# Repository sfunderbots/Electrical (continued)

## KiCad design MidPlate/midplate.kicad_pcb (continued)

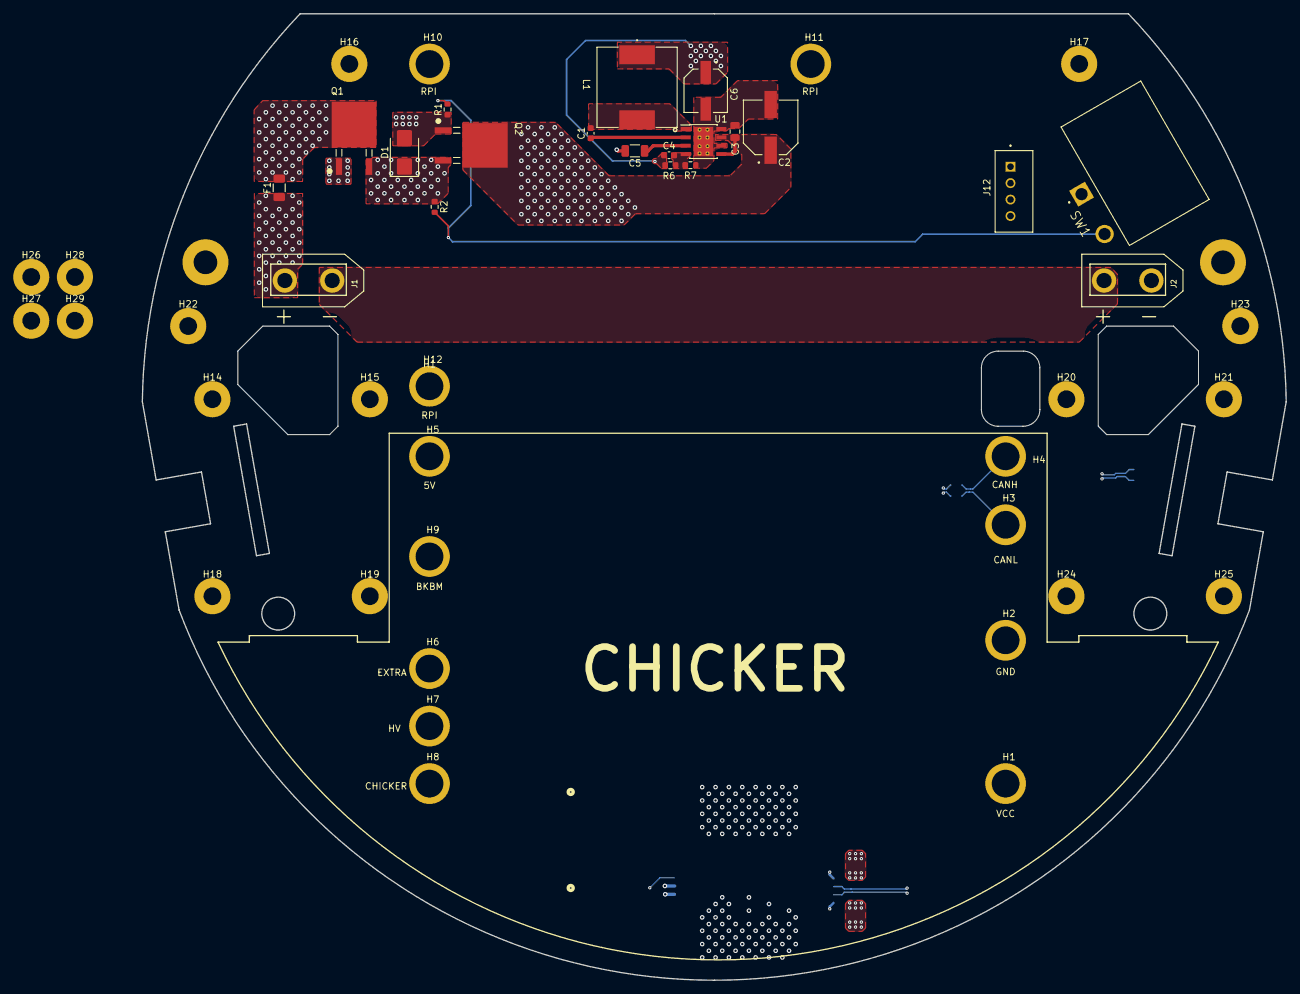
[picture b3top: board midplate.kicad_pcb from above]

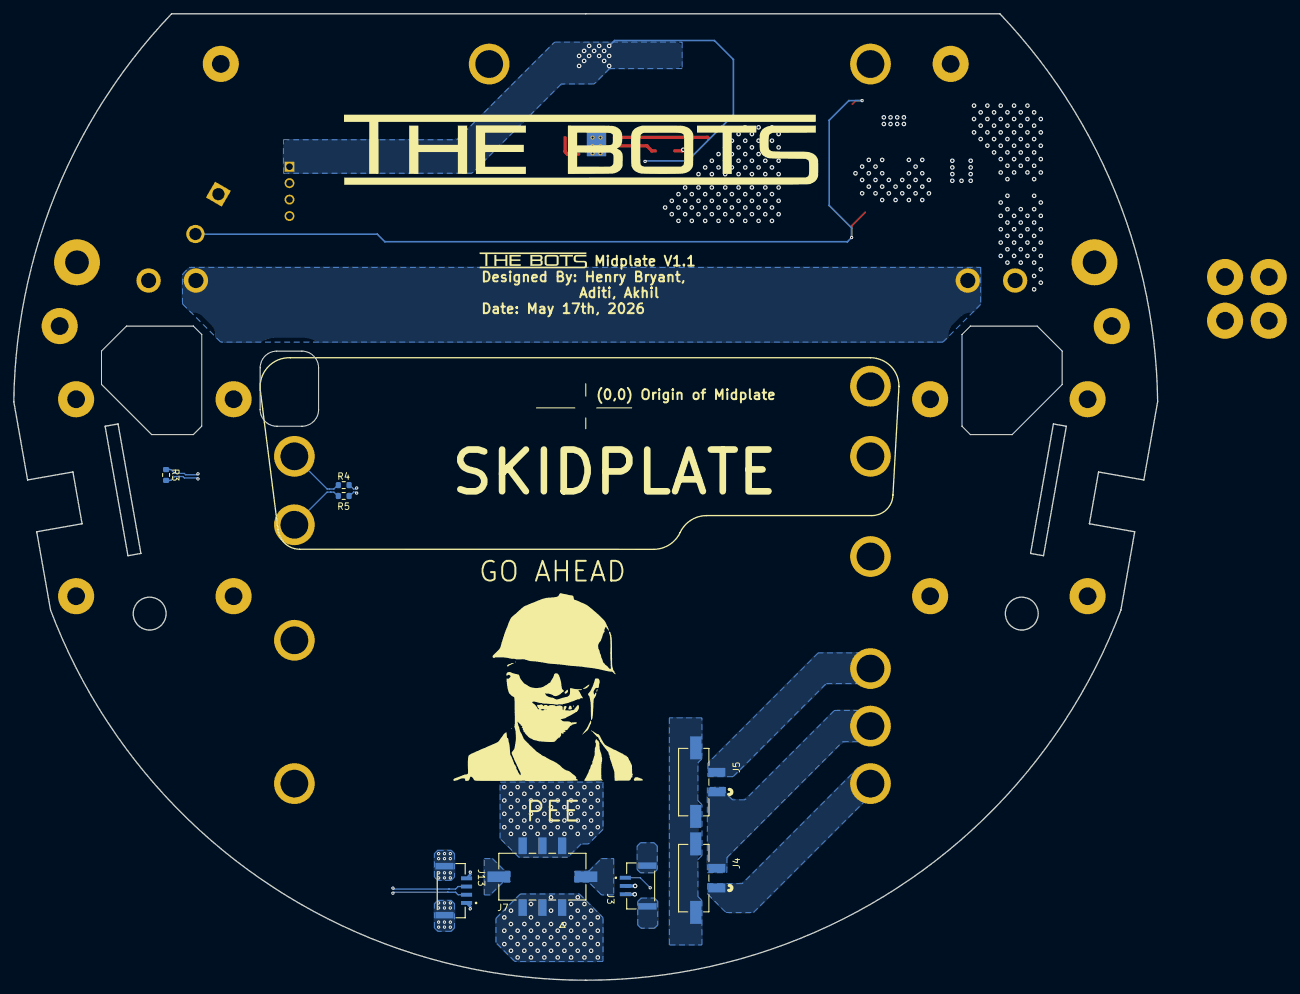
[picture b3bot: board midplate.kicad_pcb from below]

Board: 4 copper layers, 174.0 x 147.0 mm, 59 parts (8 on the bottom side), 22 nets.

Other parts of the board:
H1#2: RPI; MountingHole_2.7mm_M2.5_DIN965_Pad
H47, H48: MountingHoleM2.5NoThread; MountingHole_3.6mm_M3_clearance

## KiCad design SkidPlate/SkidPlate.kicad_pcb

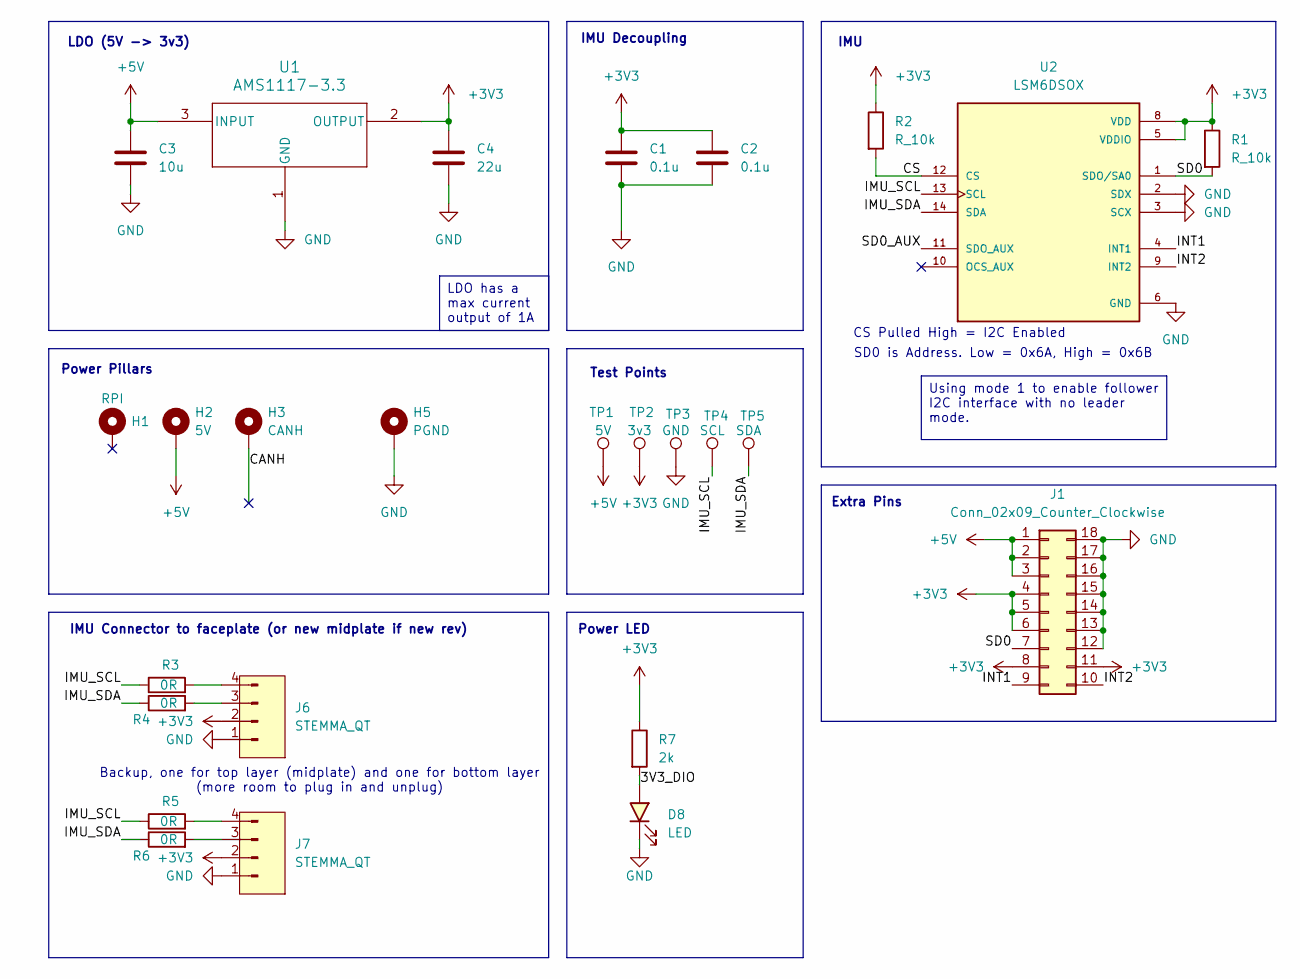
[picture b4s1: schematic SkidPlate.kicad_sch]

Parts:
C1, C2: 0.1u; C_0603_1608Metric; MPN CC0603KRX7R9BB104; JLC 0603
C3: 10u; C_0805_2012Metric; MPN GRM21BR61H106KE43L; JLC 0805
C4: 22u; C_0603_1608Metric; LCSC C59461
D8: LED; LED_0805_2012Metric; MPN KT-0805G; JLC 0805
H1: RPI; MountingHole_2.7mm_M2.5_DIN965_Pad
H2: 5V; MountingHole_2.7mm_M2.5_DIN965_Pad
H3: CANH; MountingHole_2.7mm_M2.5_DIN965_Pad
H5: PGND; MountingHole_2.7mm_M2.5_DIN965_Pad
J1: Conn_02x09_Counter_Clockwise; PinHeader_2x09_P2.54mm_Vertical
J6, J7: STEMMA_QT; JST_SH_BM04B-SRSS-TB_1x04-1MP_P1.00mm_Vertical
R1, R2: R_10k; R_0603_1608Metric; MPN 0603WAF1002T5E; JLC 0603
R3, R4, R5, R6: 0R; R_0603_1608Metric; MPN 0603WAF0000T5E; JLC 0603
R7: 2k; R_0603_1608Metric; MPN 0603WAF2001T5E; JLC 0603
TP1: 5V; TestPoint_Pad_D1.0mm
TP2: 3v3; TestPoint_Pad_D1.0mm
TP3: GND; TestPoint_Pad_D1.0mm
TP4: SCL; TestPoint_Pad_D1.0mm
TP5: SDA; TestPoint_Pad_D1.0mm
U1: AMS1117-3.3; SOT-223-3_TabPin2; MPN AMS1117-3.3; JLC SOT-223
U2: LSM6DSOX; PQFN50P250X300X86-14N; PARTREV 3.0; JLC LGA-14(2.5x3)

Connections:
+3V3: C1.1, C2.1, C4.1, J1.4, J1.5, J1.6, J1.8, J1.11, J6.2, J7.2, R1.1, R2.1, R7.1, TP2.1 (1_1), U1.2 (OUTPUT), U2.5 (VDDIO), U2.8 (VDD)
+5V: C3.1, H2.1 (1_1), J1.1, J1.2, J1.3, TP1.1 (1_1), U1.3 (INPUT)
/3V3_DIO: D8.2 (A), R7.2
/CANH: H3.1 (1_1)
/CS: R2.2, U2.12 (CS)
/IMU_SCL: R3.1, R5.1, TP4.1 (1_1), U2.13 (SCL)
/IMU_SDA: R4.1, R6.1, TP5.1 (1_1), U2.14 (SDA)
/INT1: J1.9, U2.4 (INT1)
/INT2: J1.10, U2.9 (INT2)
/SD0: J1.7, R1.2, U2.1 (SDO/SA0)
/SD0_AUX: U2.11 (SDO_AUX)
GND: C1.2, C2.2, C3.2, C4.2, D8.1 (K), H5.1 (1_1), J1.12, J1.13, J1.14, J1.15, J1.16, J1.17, J1.18, J6.1, J7.1, TP3.1 (1_1), U1.1 (GND), U2.2 (SDX), U2.3 (SCX), U2.6 (GND), U2.7 (GND)
unnamed: J6.3, R4.2
unnamed: J6.4, R3.2
unnamed: J7.3, R6.2
unnamed: J7.4, R5.2

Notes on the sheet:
IMU Connector to faceplate (or new midplate if new rev)
Backup, one for top layer (midplate) and one for bottom layer (more room to plug in and unplug)
Extra Pins
Test Points
IMU
CS Pulled High = I2C Enabled
Power Pillars
Power LED
LDO (5V -> 3v3)
IMU Decoupling
SD0 is Address. Low = 0x6A, High = 0x6B
LDO has a max current output of 1A
Using mode 1 to enable follower I2C interface with no leader mode.

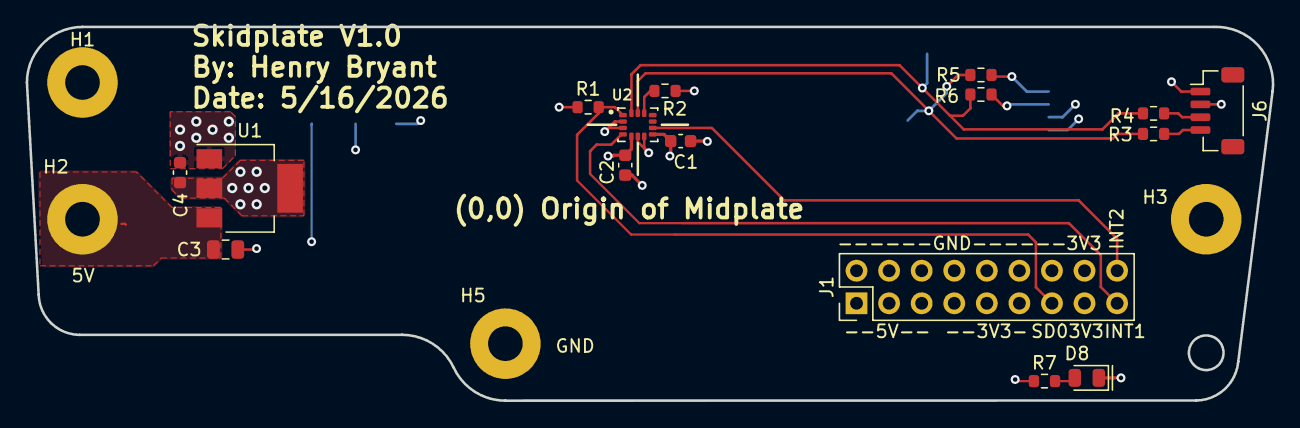
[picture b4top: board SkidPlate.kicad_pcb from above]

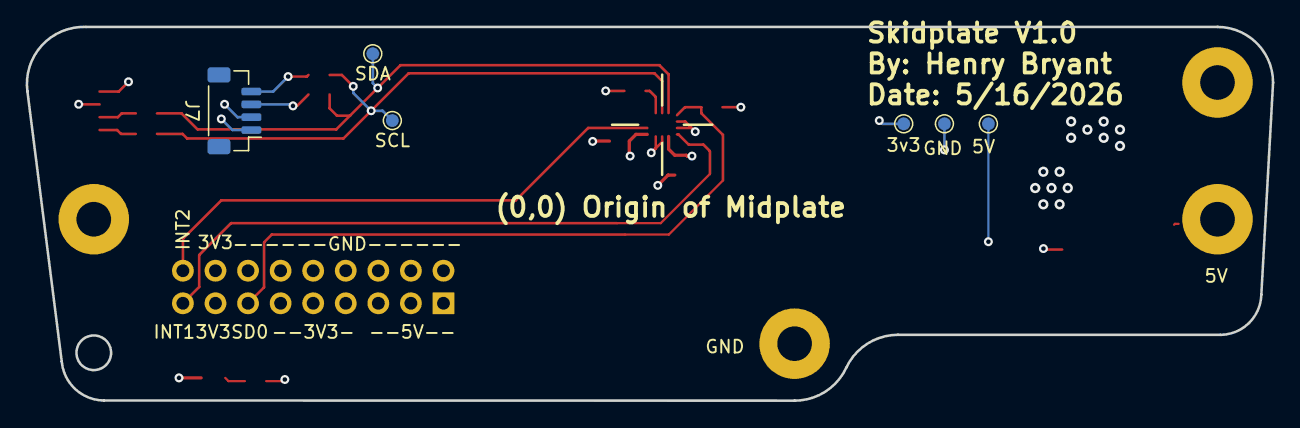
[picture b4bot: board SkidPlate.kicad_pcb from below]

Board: 4 copper layers, 97.2 x 29.1 mm, 26 parts (6 on the bottom side), 14 nets.

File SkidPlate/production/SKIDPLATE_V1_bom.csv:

Designator,Footprint,Quantity,Value,LCSC Part #
"C1, C2",0603,2,0.1u,C14663
C3,0805,1,10u,C440198
C4,0603,1,22u,C59461
D8,0805,1,LED,C2297
H2,MountingHole_2.7mm_M2.5_DIN965_Pad,1,PGND,
H5,MountingHole_2.7mm_M2.5_DIN965_Pad,1,5V,
H6,MountingHole_2.7mm_M2.5_DIN965_Pad,1,EXTRA,
H9,MountingHole_2.7mm_M2.5_DIN965_Pad,1,BKBM,
J1,PinHeader_2x09_P2.54mm_Vertical,1,Conn_02x09_Counter_Clockwise,
"J6, J7",JST_SH_BM04B-SRSS-TB_1x04-1MP_P1.00mm_Vertical,2,STEMMA_QT,
"R1, R2",0603,2,R_10k,C25804
"R3, R4, R5, R6",0603,4,0R,C21189
R7,0603,1,2k,C22975
TP1,TestPoint_Pad_D1.0mm,1,5V,
TP2,TestPoint_Pad_D1.0mm,1,3v3,
TP3,TestPoint_Pad_D1.0mm,1,GND,
TP4,TestPoint_Pad_D1.0mm,1,SCL,
TP5,TestPoint_Pad_D1.0mm,1,SDA,
U1,SOT-223-3_TabPin2,1,AMS1117-3.3,C6186
U2,PQFN50P250X300X86-14N,1,LSM6DSOX,C2655100

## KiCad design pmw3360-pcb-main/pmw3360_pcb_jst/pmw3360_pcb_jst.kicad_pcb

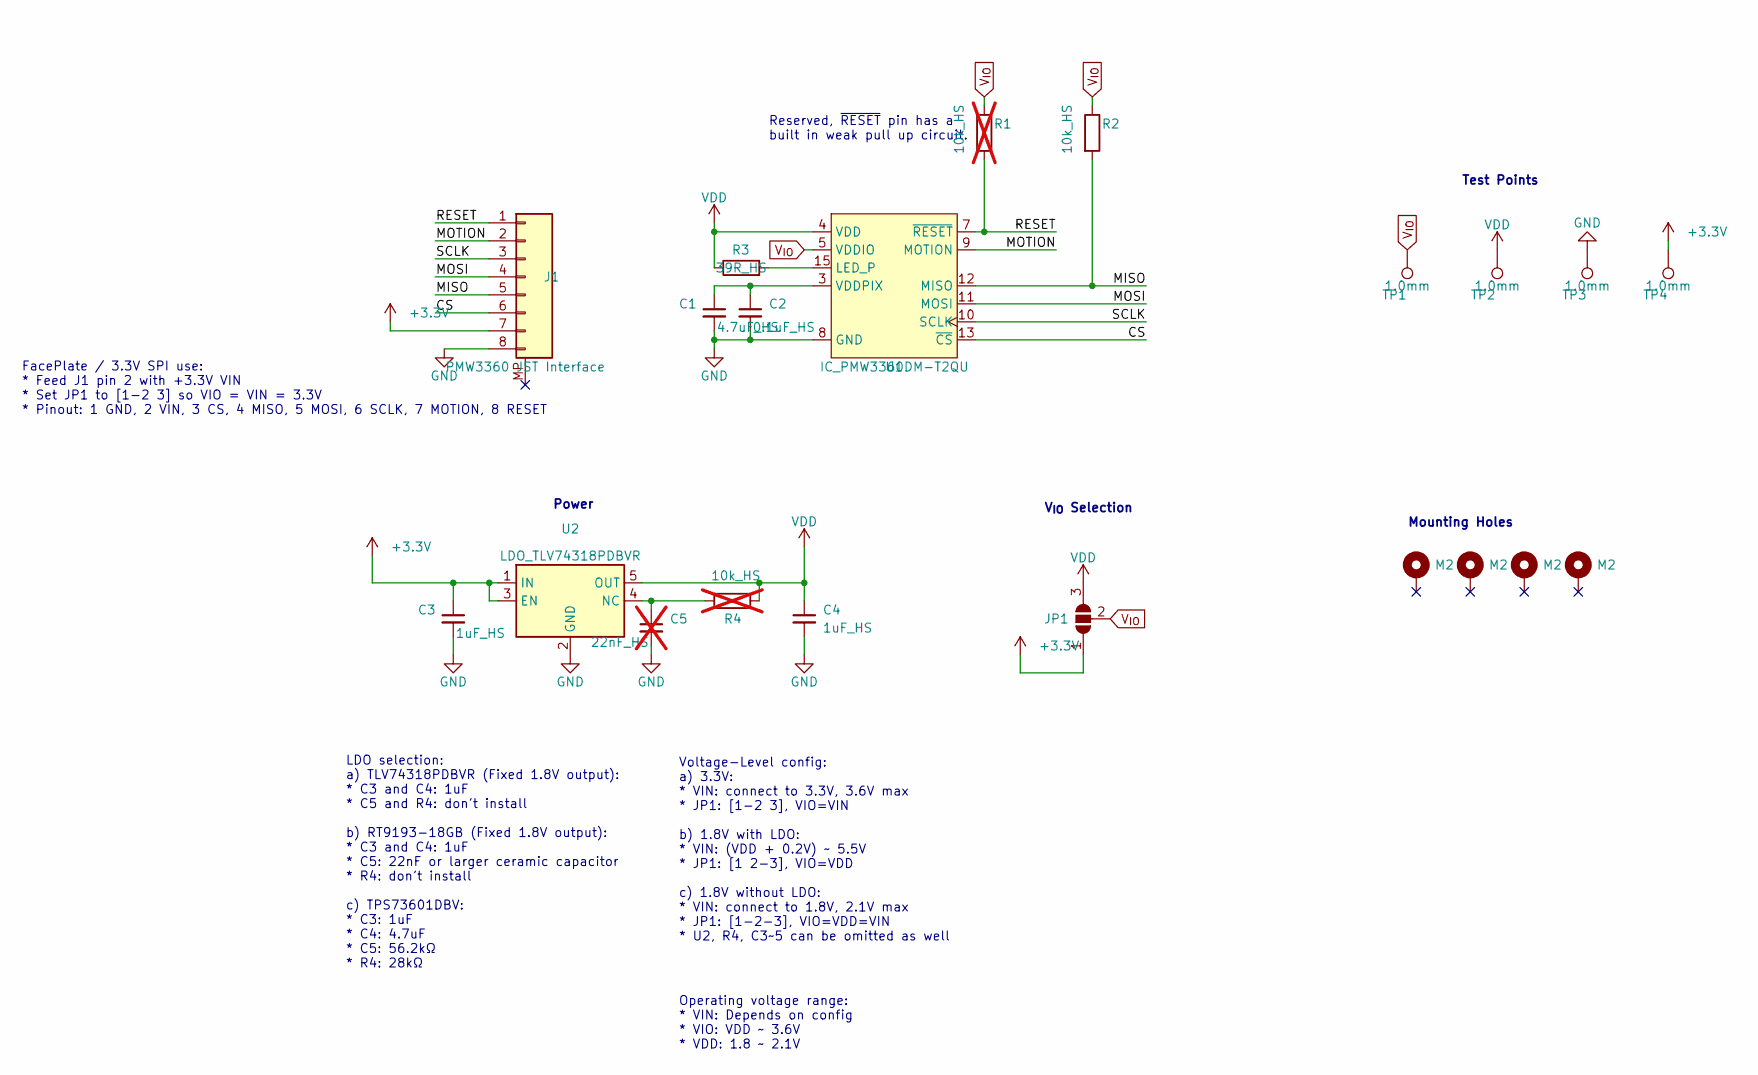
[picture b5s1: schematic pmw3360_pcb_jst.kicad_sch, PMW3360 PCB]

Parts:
C1: 4.7uF_HS; C_0603_1608Metric_Pad1.08x0.95mm_HandSolder; MPN CL10A475KO8NNNC; LCSC C19666
C2: 0.1uF_HS; C_0603_1608Metric_Pad1.08x0.95mm_HandSolder; MPN CC0603KRX7R9BB104; LCSC C14663
C3, C4: 1uF_HS; C_0603_1608Metric_Pad1.08x0.95mm_HandSolder; MPN CL10A105KB8NNNC; LCSC C15849
C5: 22nF_HS; C_0603_1608Metric_Pad1.08x0.95mm_HandSolder; MPN CL10B223KB8NNNC; LCSC C21122; not fitted
H1, H2, H3, H4: M2; MountingHole_2.2mm_M2_ISO14580_Pad
J1: PMW3360 JST Interface; JST_BM08B-GHS-TBT_LF__SN__N_; MPN BM08B-GHS-TBT(LF)(SN); LCSC C133062
JP1: SolderJumper_3_Open; SolderJumper-3_P1.3mm_Open_RoundedPad1.0x1.5mm_NumberLabels
R1, R4: 10k_HS; R_0603_1608Metric_Pad0.98x0.95mm_HandSolder; MPN 0603WAF1002T5E; LCSC C25804; not fitted
R2: 10k_HS; R_0603_1608Metric_Pad0.98x0.95mm_HandSolder; MPN 0603WAF1002T5E; LCSC C25804
R3: 39R_HS; R_0603_1608Metric_Pad0.98x0.95mm_HandSolder; MPN 0603WAF390JT5E; LCSC C23154
TP1, TP2, TP3, TP4: 1.0mm; TestPoint_Pad_D1.0mm
U1: IC_PMW3360DM-T2QU; IC_PMW3360DM-T2QU 16Pin; MPN PMW3360DM-T2QU; LCSC C20612443
U2: LDO_TLV74318PDBVR; SOT-23-5; MPN TLV74318PDBVR; LCSC C485152

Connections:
+5V: C3.1, J1.7, JP1.1 (A), TP4.1, U2.1 (IN), U2.3 (EN)
/CS: J1.6, U1.13 (~CS)
/MISO: J1.5, R2.2, U1.12 (MISO)
/MOSI: J1.4, U1.11 (MOSI)
/MOTION: J1.2, U1.9 (MOTION)
/RESET: J1.1, R1.2, U1.7 (~RESET)
/SCLK: J1.3, U1.10 (SCLK)
GND: C1.2, C2.2, C3.2, C4.2, C5.2, J1.8, TP3.1, U1.8 (GND), U2.2 (GND)
unnamed: R3.2, U1.15 (LED_P)
unnamed: C1.1, C2.1, U1.3 (VDDPIX)
unnamed: C5.1, R4.2, U2.4 (NC)
VDD: C4.1, JP1.3 (B), R3.1, R4.1, TP2.1, U1.4 (VDD), U2.5 (OUT)
V_{IO}: JP1.2 (C), R1.1, R2.1, TP1.1, U1.5 (VDDIO)

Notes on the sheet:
Mounting Holes
Test Points
V_{IO} Selection
LDO selection: a) TLV74318PDBVR (Fixed 1.8V output): * C3 and C4: 1uF * C5 and R4: don't install b) RT9193-18GB (Fixed 1.8V output): * C3 and C4: 1uF * C5: 22nF or larger ceramic capacitor * R4: don't install c) TPS73601DBV: * C3: 1uF * C4: 4.7uF * C5: 56.2kΩ * R4: 28kΩ
Operating voltage range: * VIN: Depends on config * VIO: VDD ~ 3.6V * VDD: 1.8 ~ 2.1V
Power
FacePlate / 3.3V SPI use: * Feed J1 pin 2 with +3.3V VIN * Set JP1 to [1-2 3] so VIO = VIN = 3.3V * Pinout: 1 GND, 2 VIN, 3 CS, 4 MISO, 5 MOSI, 6 SCLK, 7 MOTION, 8 RESET
Reserved, ~{RESET} pin has a built in weak pull up circuit.
Voltage-Level config: a) 3.3V: * VIN: connect to 3.3V, 3.6V max * JP1: [1-2 3], VIO=VIN b) 1.8V with LDO: * VIN: (VDD + 0.2V) ~ 5.5V * JP1: [1 2-3], VIO=VDD c) 1.8V without LDO: * VIN: connect to 1.8V, 2.1V max * JP1: [1-2-3], VIO=VDD=VIN * U2, R4, C3~5 can be omitted as well

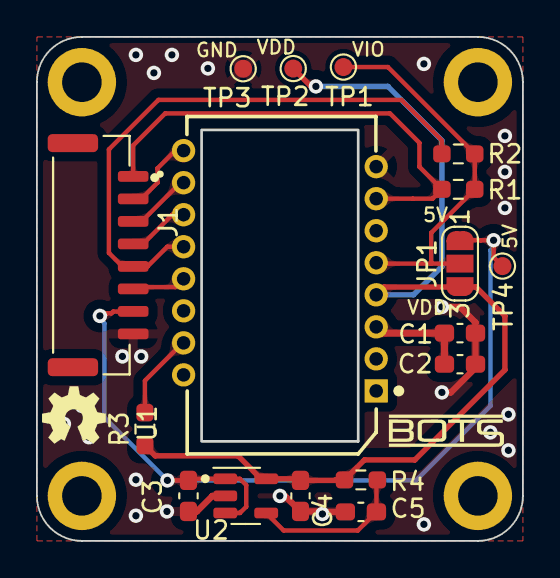
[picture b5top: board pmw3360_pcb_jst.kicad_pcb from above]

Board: 2 copper layers, 27.0 x 28.0 mm, 21 parts (0 on the bottom side), 13 nets.

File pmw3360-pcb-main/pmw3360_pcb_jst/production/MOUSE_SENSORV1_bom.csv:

Designator,Footprint,Quantity,Value,LCSC Part #
C1,0603,1,4.7uF_HS,C19666
C2,0603,1,0.1uF_HS,C14663
"C3, C4",0603,2,1uF_HS,C15849
J1,JST_BM08B-GHS-TBT_LF__SN__N_,1,JST_BM08B-GHS-TBT,C133062
R2,0603,1,10k_HS,C25804
R3,0603,1,39R_HS,C23154
"TP1, TP2, TP3, TP4",TestPoint_Pad_D1.0mm,4,1.0mm,
U1,IC_PMW3360DM-T2QU 16Pin,1,IC_PMW3360DM-T2QU,C20612443
U2,SOT-23-5,1,LDO_TLV74318PDBVR,C485152

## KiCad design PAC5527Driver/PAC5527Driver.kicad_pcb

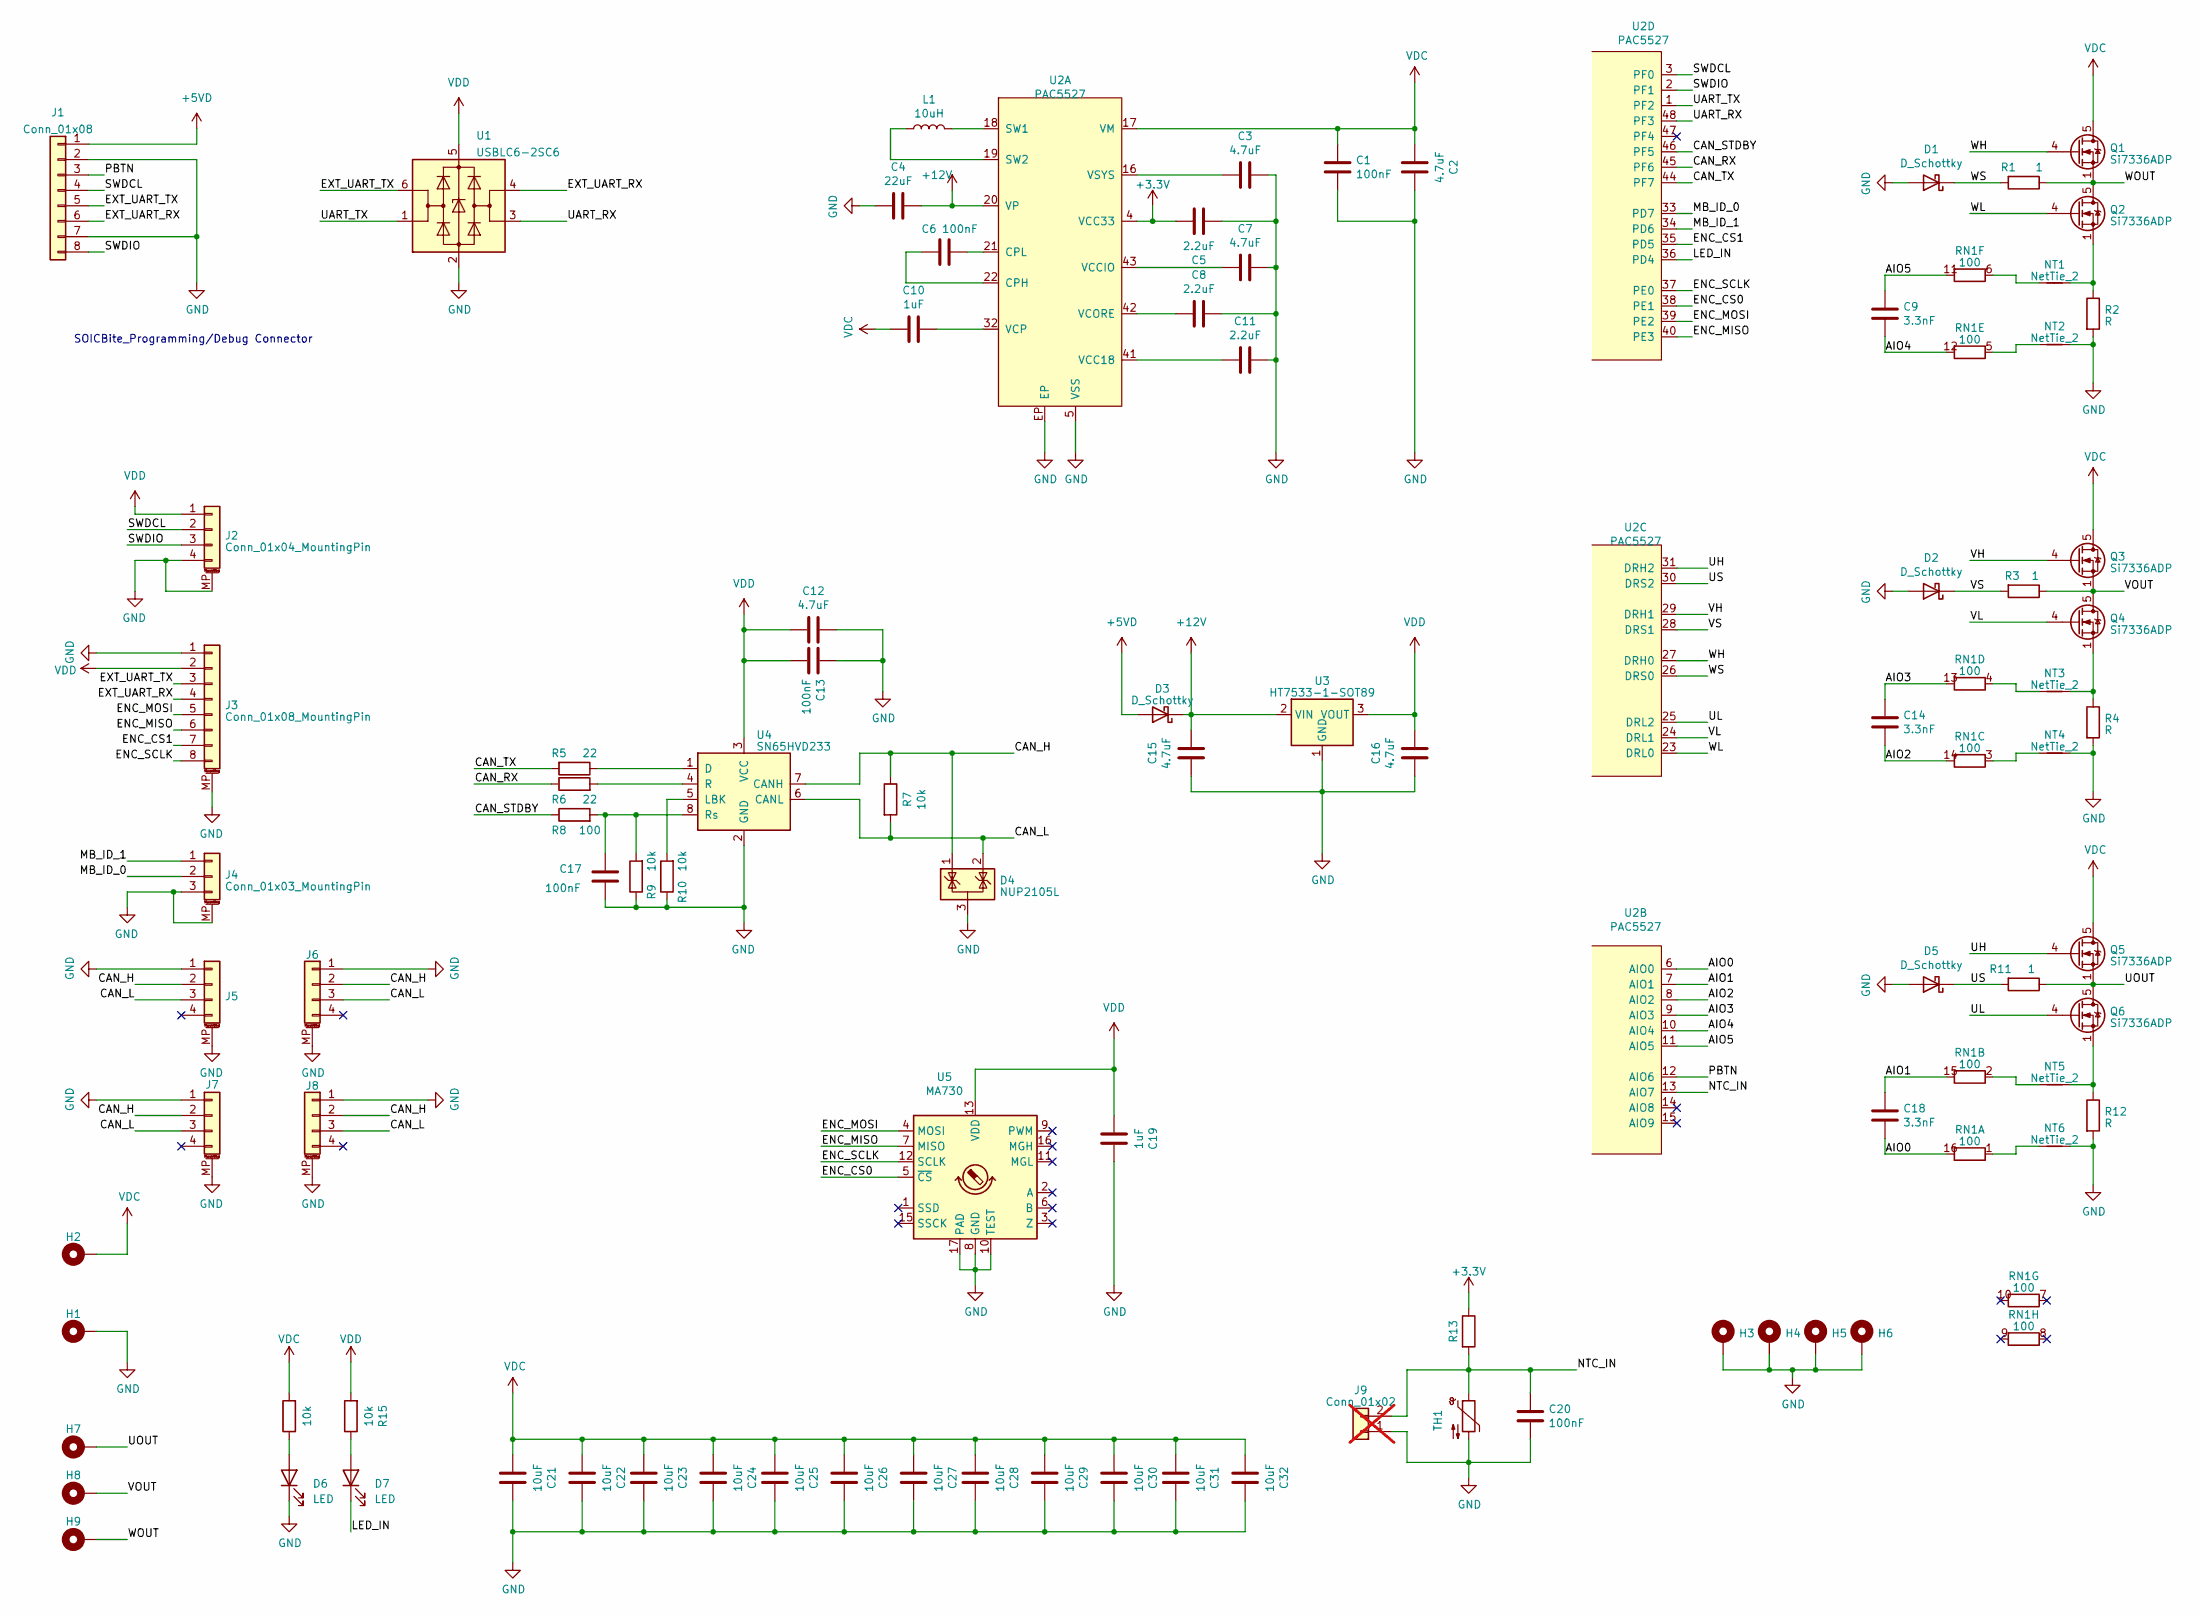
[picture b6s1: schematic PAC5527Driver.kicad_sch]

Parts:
C1: 100nF; C_0603_1608Metric
C2, C3, C7, C12, C15, C16: 4.7uF; C_0402_1005Metric
C4: 22uF; C_0805_2012Metric
C5, C8, C11: 2.2uF; C_0402_1005Metric
C6, C13, C17, C20: 100nF; C_0402_1005Metric
C9, C14, C18: 3.3nF; C_0402_1005Metric
C10, C19: 1uF; C_0402_1005Metric
C21, C22, C23, C24, C25, C26, C27, C28, C29, C30, C31, C32: 10uF; C_1210_3225Metric
D1, D2, D3, D5: D_Schottky; D_SOD-523
D4: NUP2105L; SOT-23
D6, D7: LED; D_0402_1005Metric
H1, H2: MountingHole_Pad; MountingHole_2.2mm_M2_DIN965_Pad_TopBottom
H3, H4, H5, H6: MountingHole_Pad; MountingHole_2.7mm_M2.5_Pad_TopBottom
H7, H8, H9: MountingHole_Pad; MountingHole_2.2mm_M2_DIN965_Pad_TopOnly
J1: Conn_01x08; SOIC_clipProgSmall
J2, J6, J8: Conn_01x04_MountingPin; JST_GH_BM04B-GHS-TBT_1x04-1MP_P1.25mm_Vertical
J3: Conn_01x08_MountingPin; JST_GH_BM08B-GHS-TBT_1x08-1MP_P1.25mm_Vertical
J4: Conn_01x03_MountingPin; JST_GH_BM03B-GHS-TBT_1x03-1MP_P1.25mm_Vertical
J5, J7: Conn_01x04_MountingPin; JST_GH_SM04B-GHS-TB_1x04-1MP_P1.25mm_Horizontal
J9: Conn_01x02; PinHeader_1x02_P1.27mm_Vertical; not fitted
L1: 10uH; L_Changjiang_FNR3010S
NT1, NT2, NT3, NT4, NT5, NT6: NetTie_2; NetTie-2_SMD_Pad0.5mm
Q1, Q2, Q3, Q4, Q5, Q6: Si7336ADP; PowerPAK_SO-8_Single
R1, R3, R11: 1; R_0402_1005Metric
R2, R4, R12: R; R_2512_6332Metric
R5, R6: 22; R_0402_1005Metric
R7, R9, R10, R13, R14, R15: 10k; R_0402_1005Metric
R8: 100; R_0402_1005Metric
RN1: 100; R_Array_Convex_8x0602
TH1: Thermistor_NTC; R_0402_1005Metric
U1: USBLC6-2SC6; SOT-23-6
U2: PAC5527; QFN-48-1EP_6x6mm_P0.4mm_EP4.3x4.3mm_ThermalVias
U3: HT7533-1-SOT89; SOT-89-3
U4: SN65HVD233; SOIC-8_3.9x4.9mm_P1.27mm
U5: MA730; QFN-16-1EP_3x3mm_P0.5mm_EP1.7x1.7mm

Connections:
+3.3V: C5.1, R13.1, U2.4 (VCC33)
+5VD: D3.2 (A), J1.1
+12V: C4.2, C15.2, D3.1 (K), U2.20 (VP), U3.2 (VIN)
/AIO0: C18.2, RN1.16 (R1.2), U2.6 (AIO0)
/AIO1: C18.1, RN1.15 (R2.2), U2.7 (AIO1)
/AIO2: C14.2, RN1.14 (R3.2), U2.8 (AIO2)
/AIO3: C14.1, RN1.13 (R4.2), U2.9 (AIO3)
/AIO4: C9.2, RN1.12 (R5.2), U2.10 (AIO4)
/AIO5: C9.1, RN1.11 (R6.2), U2.11 (AIO5)
/CAN_H: D4.1 (K), J5.2, J6.2, J7.2, J8.2, R7.1, U4.7 (CANH)
/CAN_L: D4.2 (K), J5.3, J6.3, J7.3, J8.3, R7.2, U4.6 (CANL)
/CAN_RX: R6.1, U2.45 (PF6)
/CAN_STDBY: R8.1, U2.46 (PF5)
/CAN_TX: R5.2, U2.44 (PF7)
/ENC_CS0: U2.38 (PE1), U5.5 (~CS)
/ENC_CS1: J3.7, U2.35 (PD5)
/ENC_MISO: J3.6, U2.40 (PE3), U5.7 (MISO)
/ENC_MOSI: J3.5, U2.39 (PE2), U5.4 (MOSI)
/ENC_SCLK: J3.8, U2.37 (PE0), U5.12 (SCLK)
/EXT_UART_RX: J1.6, J3.4, U1.4 (I/O2)
/EXT_UART_TX: J1.5, J3.3, U1.6 (I/O1)
/LED_IN: D7.1 (K), U2.36 (PD4)
/MB_ID_0: J4.2, U2.33 (PD7)
/MB_ID_1: J4.1, U2.34 (PD6)
/NTC_IN: C20.1, J9.2, R13.2, TH1.1, U2.13 (AIO7)
/PBTN: J1.3, U2.12 (AIO6)
/SWDCL: J1.4, J2.2, U2.3 (PF0)
/SWDIO: J1.8, J2.3, U2.2 (PF1)
/UART_RX: U1.3 (I/O2), U2.48 (PF3)
/UART_TX: U1.1 (I/O1), U2.1 (PF2)
/UH: Q5.4 (G), U2.31 (DRH2)
/UL: Q6.4 (G), U2.25 (DRL2)
/UOUT: H7.1, Q5.1 (S), Q5.2 (S), Q5.3 (S), Q6.5 (D), R11.1
/US: D5.1 (K), R11.2, U2.30 (DRS2)
/VH: Q3.4 (G), U2.29 (DRH1)
/VL: Q4.4 (G), U2.24 (DRL1)
/VOUT: H8.1, Q3.1 (S), Q3.2 (S), Q3.3 (S), Q4.5 (D), R3.1
/VS: D2.1 (K), R3.2, U2.28 (DRS1)
/WH: Q1.4 (G), U2.27 (DRH0)
/WL: Q2.4 (G), U2.23 (DRL0)
/WOUT: H9.1, Q1.1 (S), Q1.2 (S), Q1.3 (S), Q2.5 (D), R1.1
/WS: D1.1 (K), R1.2, U2.26 (DRS0)
GND: C1.2, C2.2, C3.2, C4.1, C5.2, C7.2, C8.2, C11.2, C12.2, C13.1, C15.1, C16.1, C17.1, C19.2, C20.2, C21.2, C22.2, C23.2, C24.2, C25.2, C26.2, C27.2, C28.2, C29.2, C30.2, C31.2, C32.2, D1.2 (A), D2.2 (A), D4.3 (A), D5.2 (A), D6.1 (K), H1.1, H3.1, H4.1, H5.1, H6.1, J1.2, J1.7, J2.4, J2.MP (MountPin), J3.1, J3.MP (MountPin), J4.3, J4.MP (MountPin), J5.1, J5.MP (MountPin), J6.1, J6.MP (MountPin), J7.1, J7.MP (MountPin), J8.1, J8.MP (MountPin), J9.1, NT2.2, NT4.2, NT6.2, R2.2, R4.2, R9.1, R10.1, R12.2, TH1.2, U1.2 (GND), U2.5 (VSS), U2.EP, U3.1 (GND), U4.2 (GND), U5.8 (GND), U5.10 (TEST), U5.17 (PAD)
unnamed: D6.2 (A), R14.1
unnamed: D7.2 (A), R15.1
unnamed: NT1.2, Q2.1 (S), Q2.2 (S), Q2.3 (S), R2.1
unnamed: NT3.2, Q4.1 (S), Q4.2 (S), Q4.3 (S), R4.1
unnamed: NT5.2, Q6.1 (S), Q6.2 (S), Q6.3 (S), R12.1
unnamed: NT6.1, RN1.1 (R1.1)
unnamed: NT5.1, RN1.2 (R2.1)
unnamed: NT4.1, RN1.3 (R3.1)
unnamed: NT3.1, RN1.4 (R4.1)
unnamed: NT2.1, RN1.5 (R5.1)
unnamed: NT1.1, RN1.6 (R6.1)
unnamed: C6.1, U2.22 (CPH)
unnamed: C6.2, U2.21 (CPL)
unnamed: L1.2, U2.18 (SW1)
unnamed: L1.1, U2.19 (SW2)
unnamed: C11.1, U2.41 (VCC18)
unnamed: C7.1, U2.43 (VCCIO)
unnamed: C8.1, U2.42 (VCORE)
unnamed: C10.2, U2.32 (VCP)
unnamed: C3.1, U2.16 (VSYS)
unnamed: R5.1, U4.1 (D)
unnamed: R10.2, U4.5 (LBK)
unnamed: R6.2, U4.4 (R)
unnamed: C17.2, R8.2, R9.2, U4.8 (Rs)
VDC: C1.1, C2.1, C10.1, C21.1, C22.1, C23.1, C24.1, C25.1, C26.1, C27.1, C28.1, C29.1, C30.1, C31.1, C32.1, H2.1, Q1.5 (D), Q3.5 (D), Q5.5 (D), R14.2, U2.17 (VM)
VDD: C12.1, C13.2, C16.2, C19.1, J2.1, J3.2, R15.2, U1.5 (VBUS), U3.3 (VOUT), U4.3 (VCC), U5.13 (VDD)

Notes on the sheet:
SOICBite_Programming/Debug Connector

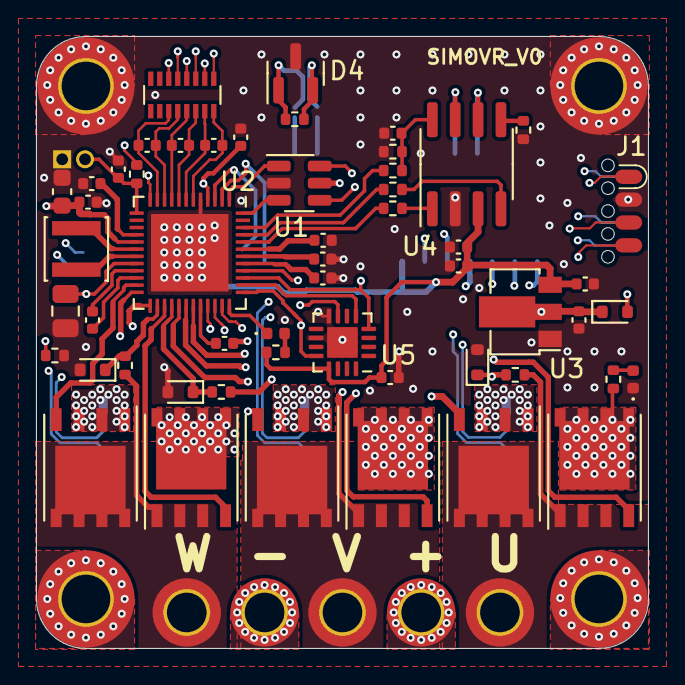
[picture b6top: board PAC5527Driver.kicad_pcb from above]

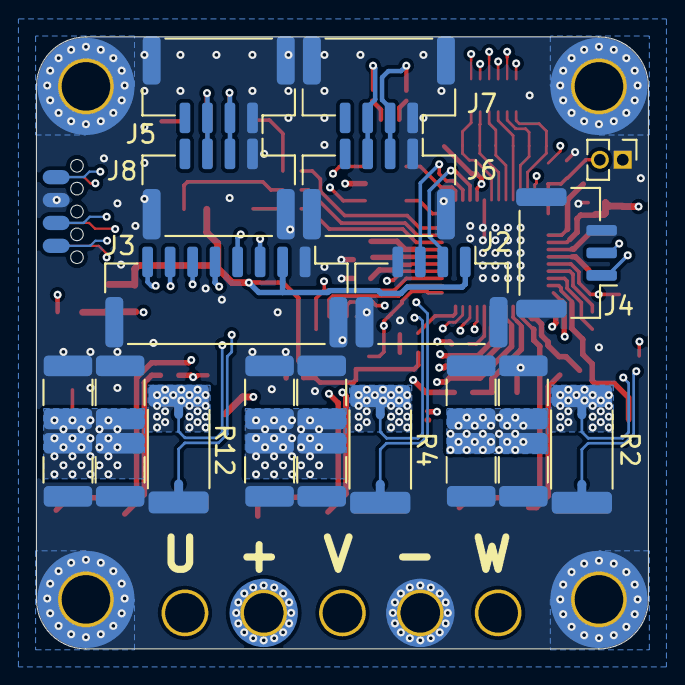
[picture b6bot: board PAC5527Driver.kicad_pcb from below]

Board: 6 copper layers, 34.0 x 34.0 mm, 92 parts (29 on the bottom side), 69 nets.
